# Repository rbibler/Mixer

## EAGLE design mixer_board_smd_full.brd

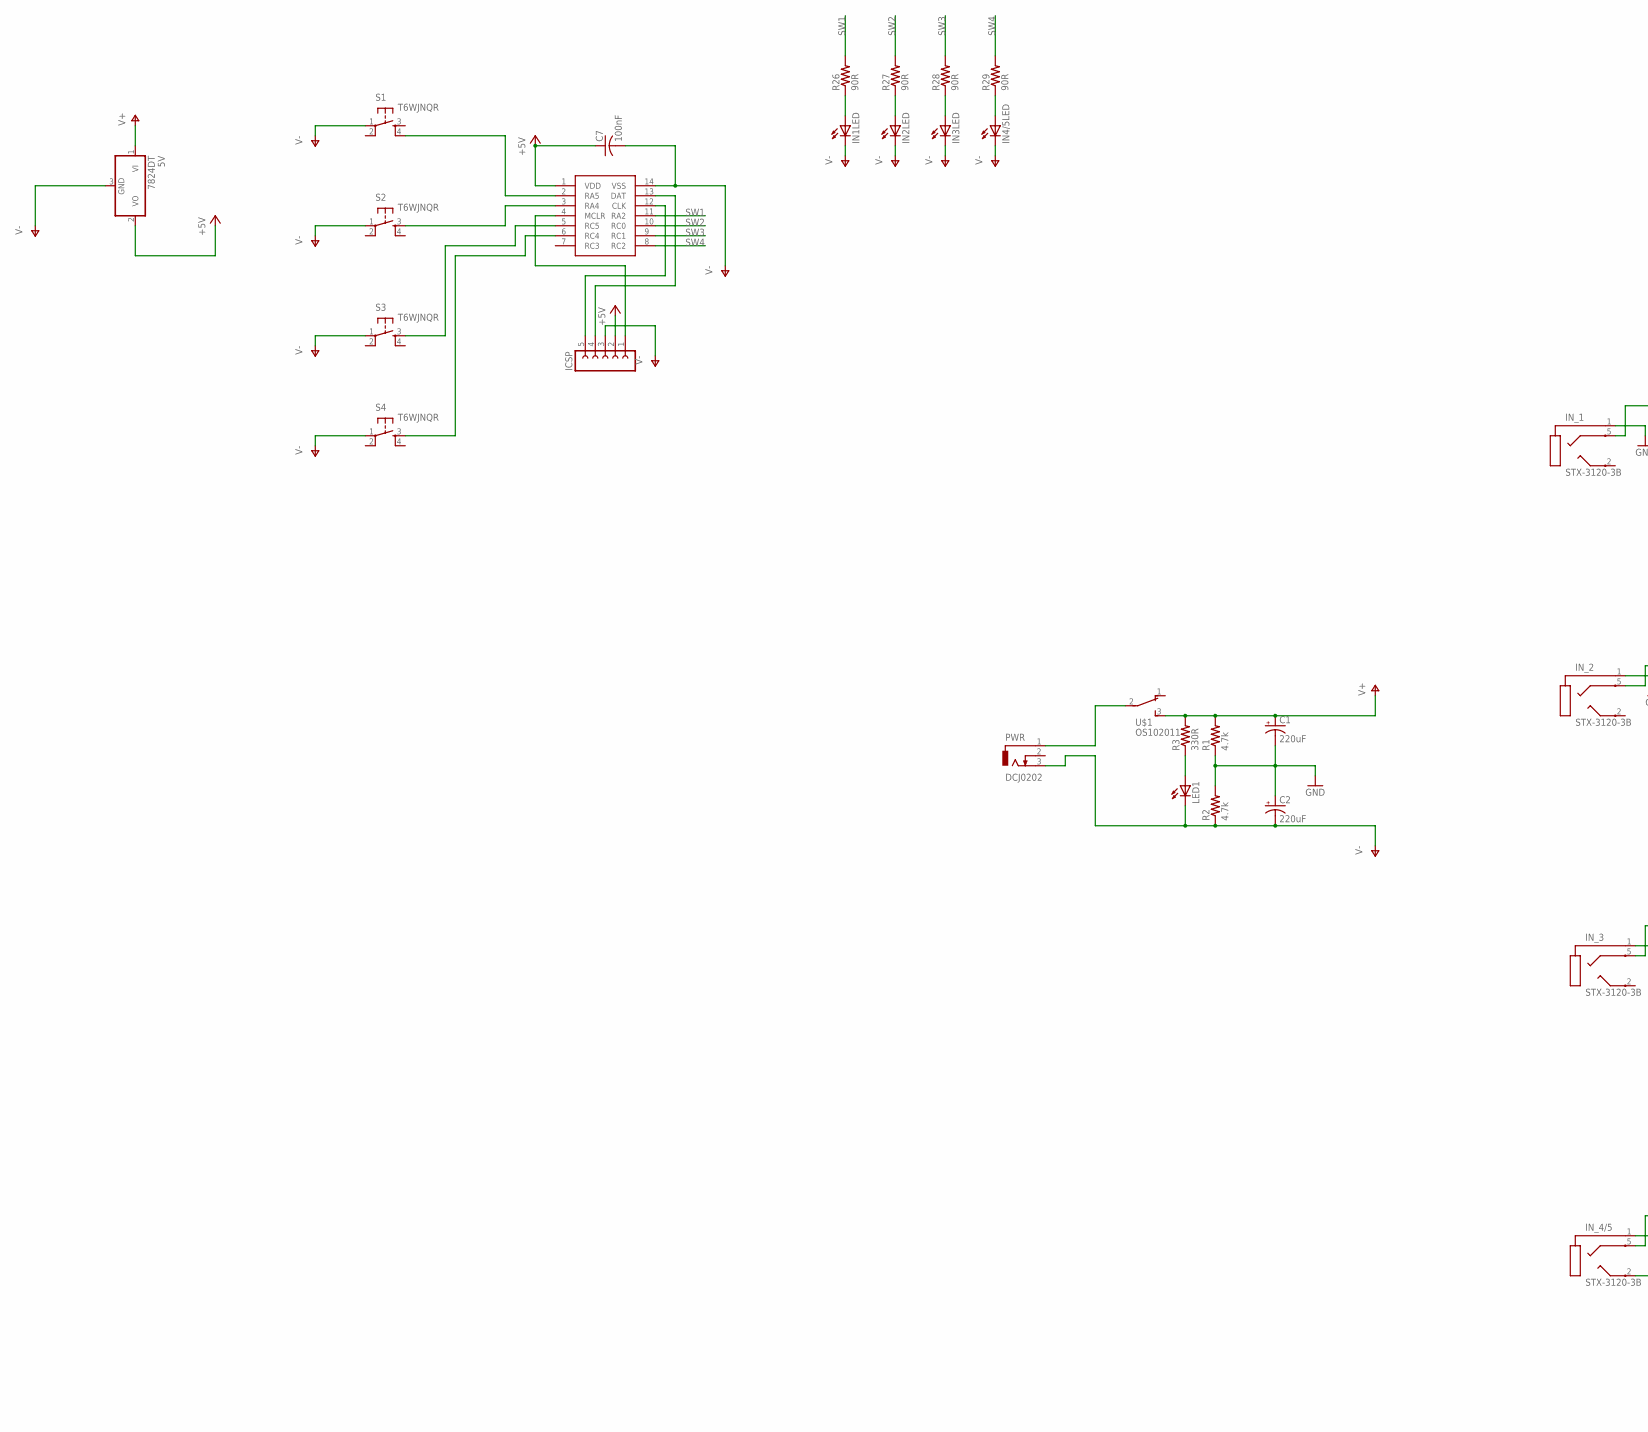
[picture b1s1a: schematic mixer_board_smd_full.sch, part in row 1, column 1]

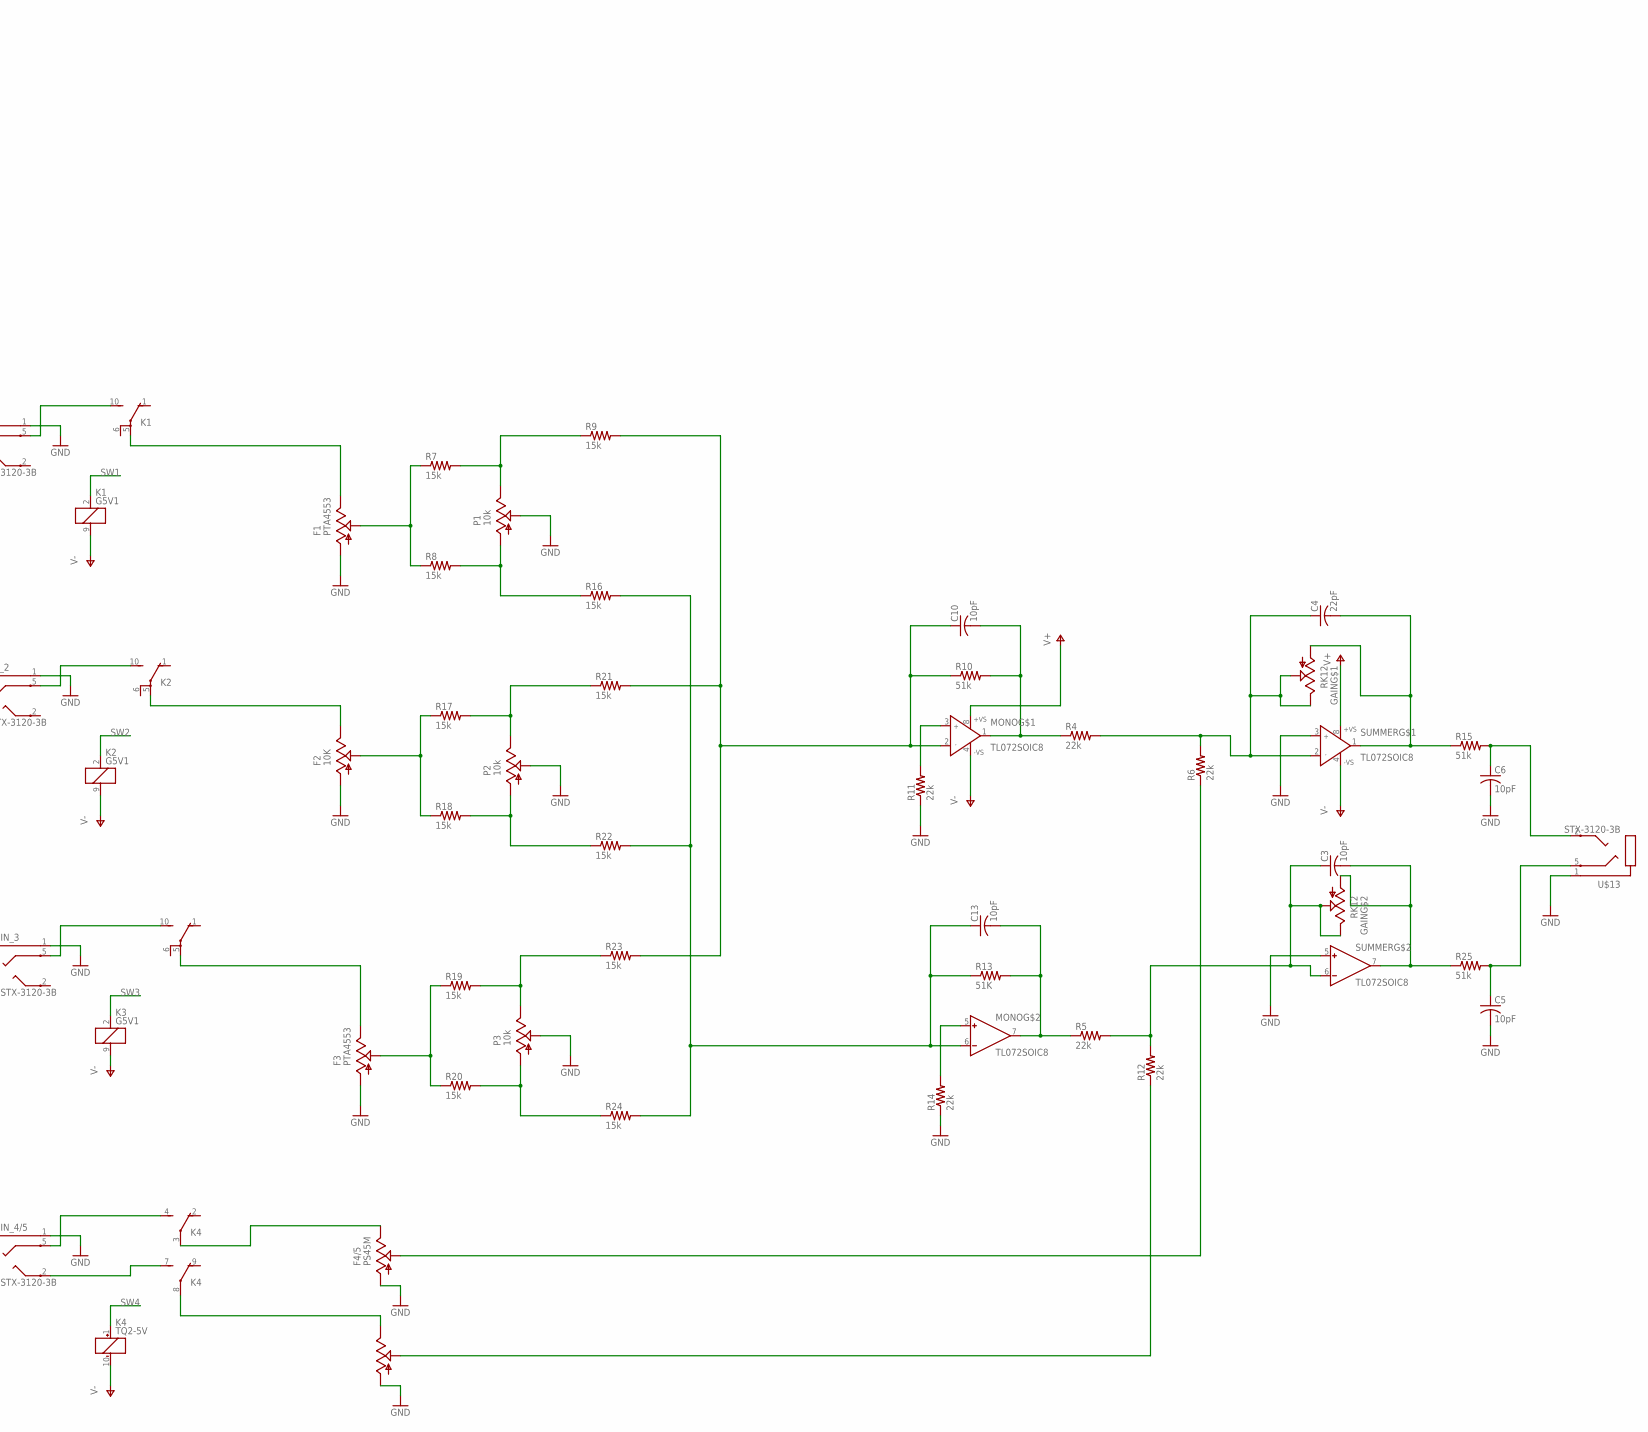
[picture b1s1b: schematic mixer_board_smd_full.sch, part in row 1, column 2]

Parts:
5V: 7824DT; TO252
C1, C2: 220uF; E1,8-4
C3, C5, C6, C10, C13: 10pF; C0805
C4: 22pF; C0805
C7: 100nF; C0805
F1, F3: PTA4553
F2: 10K; PTA4553
F4/5: PS45M
GAIN: RK12
ICSP: FE05-1
IN1LED, IN2LED, IN3LED, IN4/5LED: LEDCHIPLED_1206; CHIPLED_1206
IN_1, IN_2, IN_3, IN_4/5: STX-3120-3B; STX-3120
K1, K2, K3: G5V1
K4: TQ2-5V; TQ2
LED1: LEDCHIPLED_1206; CHIPLED_1206
MONO: TL072SOIC8; SOIC8
P1, P2, P3: 10k; PTV09A
PIC16: PIC16F18426; SO14
PWR: DCJ0202
R1, R2: 4.7k; M0805
R3: 330R; R0805
R4, R5, R6, R11, R12, R14: 22k; M0805
R7, R8, R9, R16, R17, R18, R19, R20, R21, R22, R23, R24: 15k; M0805
R10, R15, R25: 51k; M0805
R13: 51K; M0805
R26, R27, R28, R29: 90R; M0805
S1, S2, S3, S4: T6WJNQR; T6WJ2NGQR
SUMMER: TL072SOIC8; SOIC8
U$1: OS102011
U$13: STX-3120-3B; STX-3120

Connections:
+5V: 5V.2 (VO), C7.1, ICSP.2, PIC16.1 (VDD)
GND: C1.-, C2.+, C5.2, C6.2, F1.1, F2.1, F3.1, F4/5.1, F4/5.1', IN_1.1, IN_2.1, IN_3.1, IN_4/5.1, P1.2, P2.2, P3.2, R1.1, R2.2, R11.1, R14.1, SUMMER.3 (IN+), SUMMER.5 (IN+), U$13.1
unnamed: LED1.A, R3.1
unnamed: PIC16.2 (RA5), S1.4
unnamed: PIC16.3 (RA4), S2.3
unnamed: F4/5.3, K4.3
unnamed: F4/5.3', K4.8
unnamed: C4.2, GAIN.1, R15.1, SUMMER.1 (OUT)
unnamed: PIC16.5 (RC5), S3.3
unnamed: IN1LED.A, R26.1
unnamed: PIC16.6 (RC4), S4.3
unnamed: ICSP.1, PIC16.4 (MCLR)
unnamed: IN_4/5.5, K4.4 (S)
unnamed: IN_4/5.2, K4.7 (S)
unnamed: F1.2, R7.1, R8.1
unnamed: F4/5.2, R6.1
unnamed: P1.3, R7.2, R9.1
unnamed: P1.1, R8.2, R16.1
unnamed: C10.1, MONO.2 (IN-), R9.2, R10.1, R21.2, R23.2
unnamed: C10.2, MONO.1 (OUT), R4.1, R10.2
unnamed: C6.1, R15.2, U$13.2
unnamed: C4.1, GAIN.2, GAIN.3, R4.2, R6.2, SUMMER.2 (IN-)
unnamed: MONO.3 (IN+), R11.2
unnamed: P2.3, R17.2, R21.1
unnamed: C13.2, MONO.7 (OUT), R5.1, R13.2
unnamed: C5.1, R25.2, U$13.5
unnamed: MONO.5 (IN+), R14.2
unnamed: F4/5.2', R12.1
unnamed: IN2LED.A, R27.1
unnamed: C3.2, GAIN.1' (1), R25.1, SUMMER.7 (OUT)
unnamed: C13.1, MONO.6 (IN-), R13.1, R16.2, R22.2, R24.2
unnamed: P2.1, R18.2, R22.1
unnamed: IN3LED.A, R28.1
unnamed: C3.1, GAIN.2' (2), GAIN.3' (3), R5.2, R12.2, SUMMER.6 (IN-)
unnamed: IN4/5LED.A, R29.1
unnamed: P3.3, R19.2, R23.1
unnamed: P3.1, R20.2, R24.1
unnamed: F2.2, R17.1, R18.1
unnamed: ICSP.4, PIC16.13 (DAT)
unnamed: ICSP.5, PIC16.12 (CLK)
unnamed: F3.2, R19.1, R20.1
unnamed: IN_3.5, K3.10 (S)
unnamed: IN_2.5, K2.10 (S)
unnamed: IN_1.5, K1.10 (S)
unnamed: F2.3, K2.5
unnamed: F1.3, K1.5
unnamed: F3.3, K3.5
unnamed: PWR.1, U$1.2
SW1: K1.2 (1), PIC16.11 (RA2), R26.2
SW2: K2.2 (1), PIC16.10 (RC0), R27.2
SW3: K3.2 (1), PIC16.9 (RC1), R28.2
SW4: K4.1 (+), PIC16.8 (RC2), R29.2
V+: 5V.1 (VI), C1.+, MONO.8 (+VS), R1.2, R3.2, SUMMER.8 (+VS), U$1.3 (S)
V-: 5V.3 (GND), C2.-, C7.2, ICSP.3, IN1LED.C, IN2LED.C, IN3LED.C, IN4/5LED.C, K1.9 (2), K2.9 (2), K3.9 (2), K4.10 (-), LED1.C, MONO.4 (-VS), PIC16.14 (VSS), PWR.3, R2.1, S1.1, S2.1, S3.1, S4.1, SUMMER.4 (-VS)

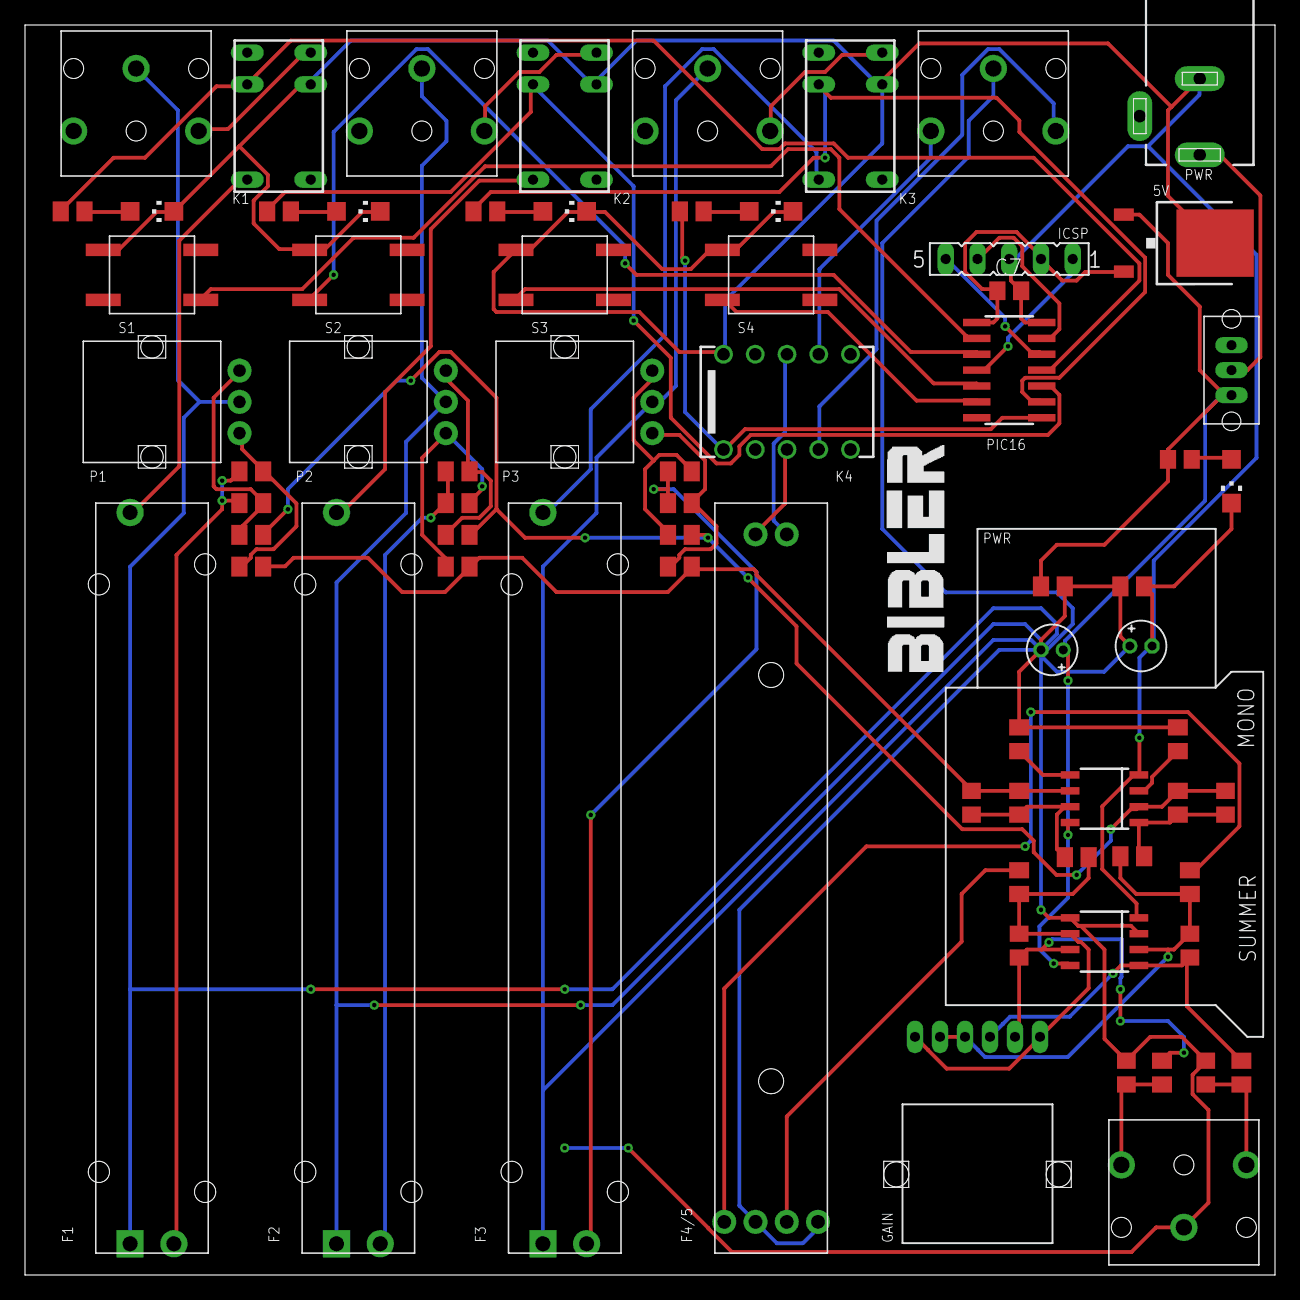
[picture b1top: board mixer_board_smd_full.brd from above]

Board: 2 copper layers, 100.0 x 100.0 mm, 71 parts (0 on the bottom side), 54 nets.

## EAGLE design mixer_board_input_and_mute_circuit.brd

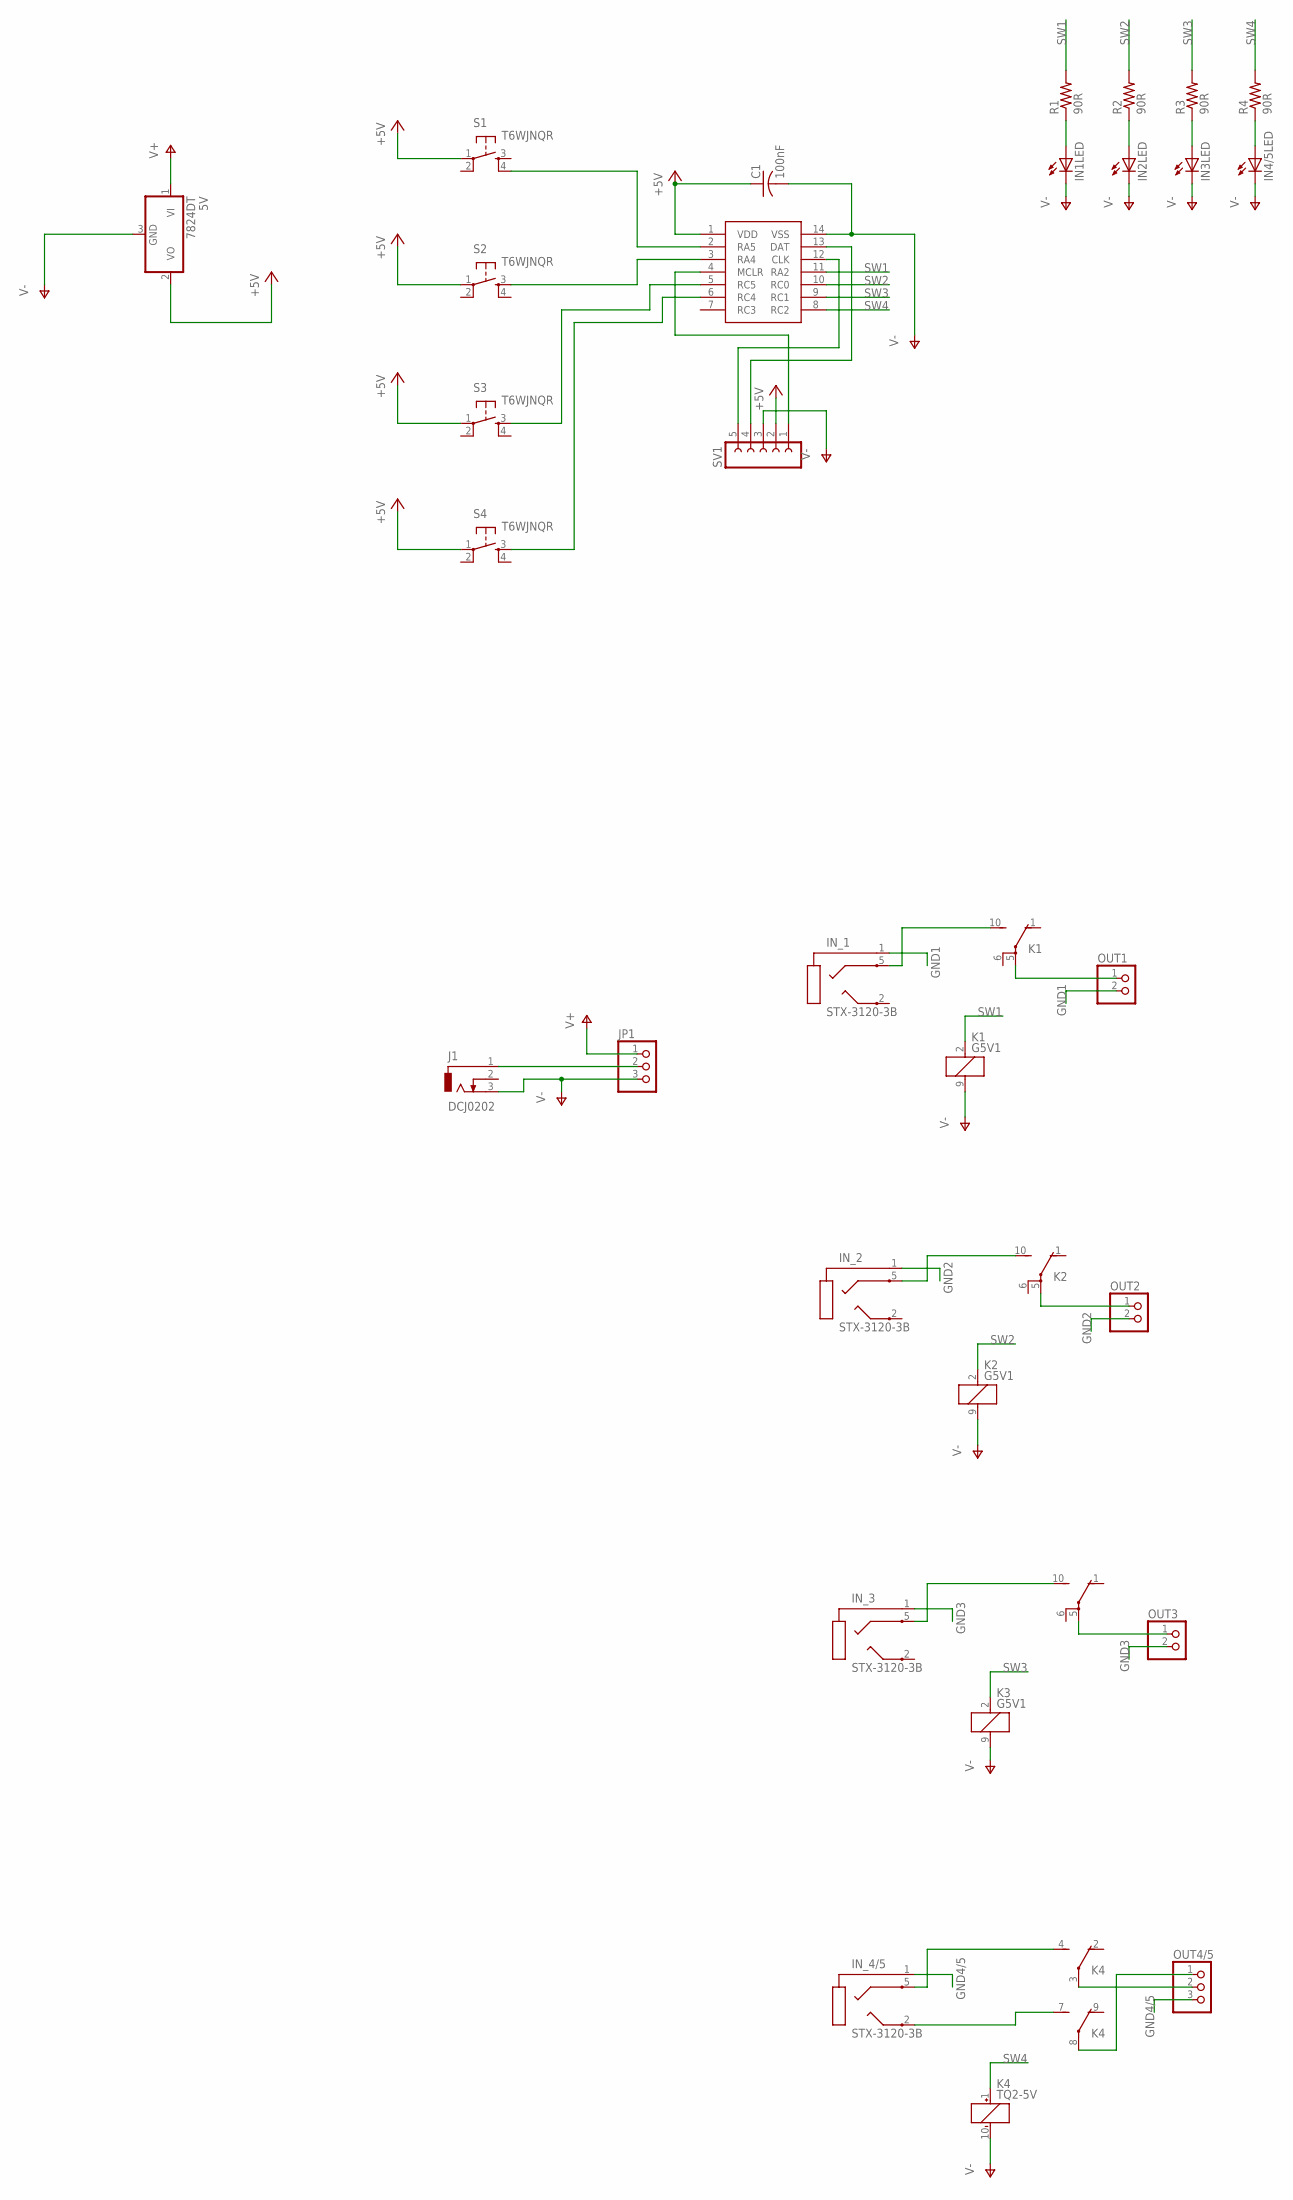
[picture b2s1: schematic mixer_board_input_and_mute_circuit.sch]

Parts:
5V: 7824DT; TO252
C1: 100nF; C0805
IN1LED, IN2LED, IN3LED, IN4/5LED: LEDCHIPLED_1206; CHIPLED_1206
IN_1, IN_2, IN_3, IN_4/5: STX-3120-3B; STX-3120
J1: DCJ0202
JP1: PINHD-1X3/90; 1X03/90
K1, K2, K3: G5V1
K4: TQ2-5V; TQ2
OUT1, OUT2, OUT3: PINHD-1X2/90; 1X02/90
OUT4/5: PINHD-1X3/90; 1X03/90
R1, R2, R3, R4: 90R; M0805
S1, S2, S3, S4: T6WJNQR; T6WJ2NGQR
SV1: FE05-1
U1: PIC16F18426; SO14

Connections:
+5V: 5V.2 (VO), C1.1, S1.1, S2.1, S3.1, S4.1, SV1.2, U1.1 (VDD)
GND1: IN_1.1, OUT1.2
GND2: IN_2.1, OUT2.2
GND3: IN_3.1, OUT3.2
GND4/5: IN_4/5.1, OUT4/5.3
unnamed: J1.1, JP1.2
unnamed: K4.3, OUT4/5.2
unnamed: S1.4, U1.2 (RA5)
unnamed: S2.3, U1.3 (RA4)
unnamed: K2.5, OUT2.1
unnamed: K1.5, OUT1.1
unnamed: K3.5, OUT3.1
unnamed: S3.3, U1.5 (RC5)
unnamed: IN1LED.A, R1.1
unnamed: S4.3, U1.6 (RC4)
unnamed: SV1.1, U1.4 (MCLR)
unnamed: IN_4/5.5, K4.4 (S)
unnamed: IN_4/5.2, K4.7 (S)
unnamed: K4.8, OUT4/5.1
unnamed: IN2LED.A, R2.1
unnamed: IN3LED.A, R3.1
unnamed: IN4/5LED.A, R4.1
unnamed: SV1.4, U1.13 (DAT)
unnamed: SV1.5, U1.12 (CLK)
unnamed: IN_3.5, K3.10 (S)
unnamed: IN_2.5, K2.10 (S)
unnamed: IN_1.5, K1.10 (S)
SW1: K1.2 (1), R1.2, U1.11 (RA2)
SW2: K2.2 (1), R2.2, U1.10 (RC0)
SW3: K3.2 (1), R3.2, U1.9 (RC1)
SW4: K4.1 (+), R4.2, U1.8 (RC2)
V+: 5V.1 (VI), JP1.1
V-: 5V.3 (GND), C1.2, IN1LED.C, IN2LED.C, IN3LED.C, IN4/5LED.C, J1.3, JP1.3, K1.9 (2), K2.9 (2), K3.9 (2), K4.10 (-), SV1.3, U1.14 (VSS)

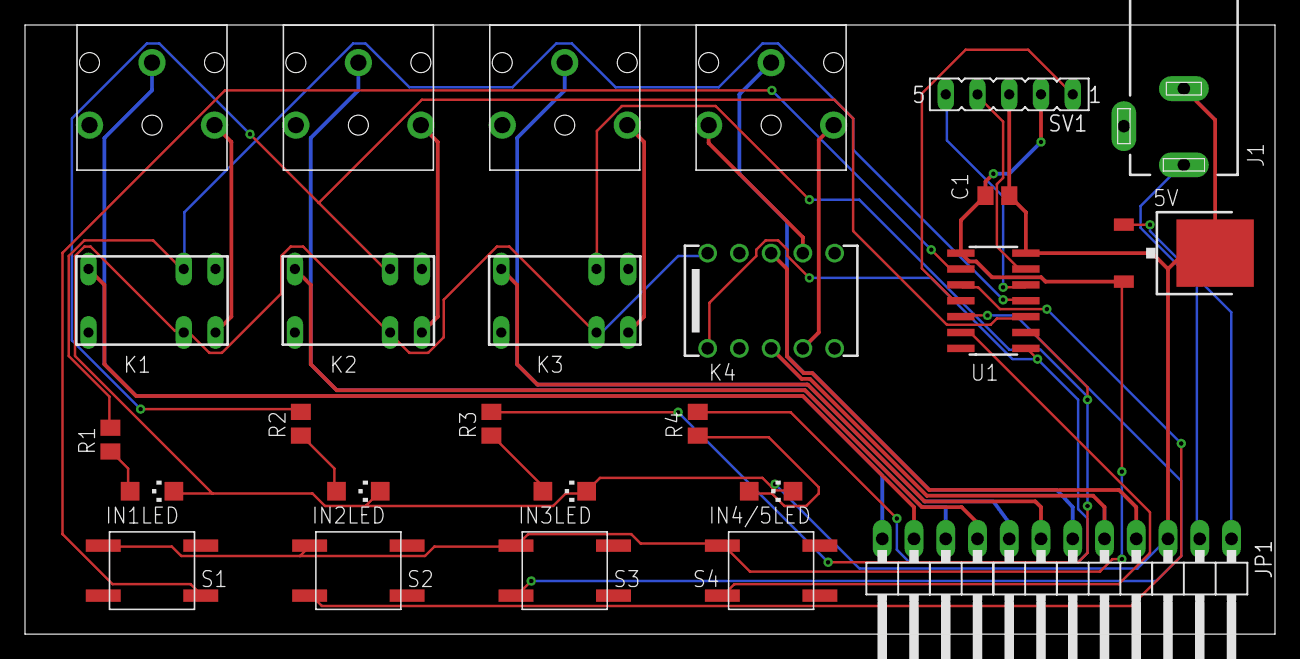
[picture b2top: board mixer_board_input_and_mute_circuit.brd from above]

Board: 2 copper layers, 100.0 x 48.7 mm, 30 parts (0 on the bottom side), 33 nets.

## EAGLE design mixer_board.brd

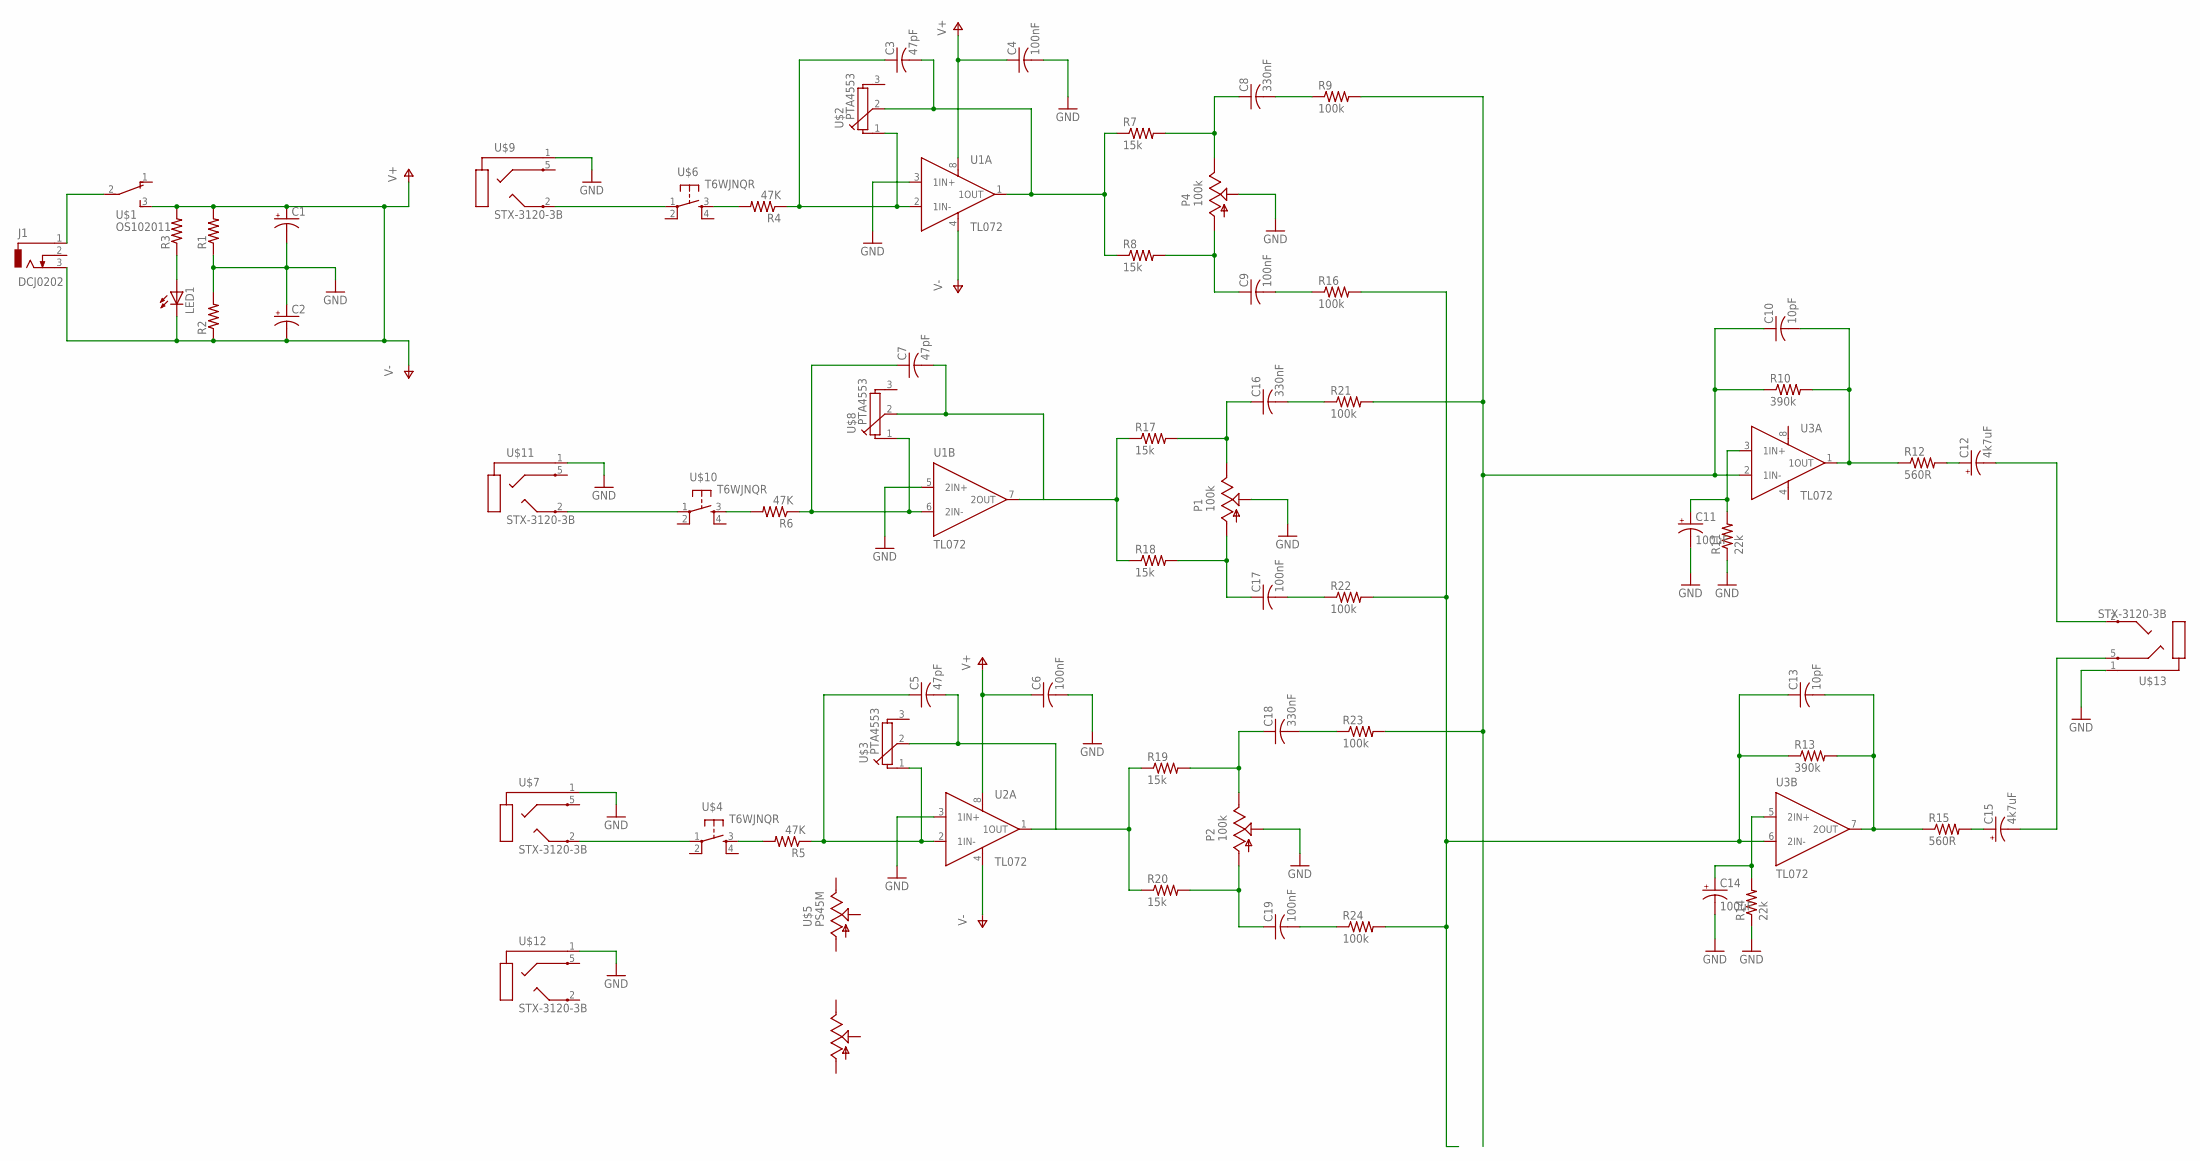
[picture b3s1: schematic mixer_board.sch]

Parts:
C1, C2: CPOL-US085CS-1R; 085CS_1R
C3, C5, C7: 47pF; C1206
C4, C6, C9, C17, C19: 100nF; C1206
C8, C16, C18: 330nF; C1206
C10, C13: 10pF; C1206
C11, C14: 100uF; 085CS_1R
C12, C15: 4k7uF; 085CS_1R
J1: DCJ0202
LED1: LEDCHIPLED_1206; CHIPLED_1206
P1, P2, P4: 100k; PTV09A
R1, R2, R3: R-US_M1406; M1406
R4, R5, R6: 47K; M1406
R7, R8, R17, R18, R19, R20: 15k; M1406
R9, R16, R21, R22, R23, R24: 100k; M1406
R10, R13: 390k; M1406
R11, R14: 22k; M1406
R12, R15: 560R; M1406
U1, U2, U3: TL072; DIP794W45P254L1060H508Q8
U$1: OS102011
U$2, U$3, U$8: PTA4553
U$4, U$6, U$10: T6WJNQR; T6WJ2NGQR
U$5: PS45M
U$7, U$9, U$11, U$12, U$13: STX-3120-3B; STX-3120

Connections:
GND: C1.-, C2.+, C4.2, C6.2, C11.-, C14.-, P1.2, P2.2, P4.2, R1.1, R2.2, R11.1, R14.1, U1.3 (1IN+), U1.5 (2IN+), U2.3 (1IN+), U$7.1, U$9.1, U$11.1, U$12.1, U$13.1
unnamed: J1.1, U$1.2
unnamed: LED1.A, R3.1
unnamed: U$4.1, U$7.2
unnamed: U$6.1, U$9.2
unnamed: C3.1, R4.1, U1.2 (1IN-), U$2.1 (1A)
unnamed: C3.2, R7.1, R8.1, U1.1 (1OUT), U$2.2 (1S)
unnamed: C5.1, R5.1, U2.2 (1IN-), U$3.1 (1A)
unnamed: R4.2, U$6.3
unnamed: C5.2, U2.1 (1OUT), U$3.2 (1S)
unnamed: R5.2, U$4.3
unnamed: U$10.1, U$11.2
unnamed: C7.1, R6.1, U1.6 (2IN-), U$8.1 (1A)
unnamed: C7.2, U1.7 (2OUT), U$8.2 (1S)
unnamed: R6.2, U$10.3
unnamed: C8.2, R9.1
unnamed: C8.1, P4.3, R7.2
unnamed: C9.1, P4.1, R8.2
unnamed: C10.1, R9.2, R10.1, R21.2, R23.2, U3.2 (1IN-)
unnamed: C10.2, R10.2, R12.1, U3.1 (1OUT)
unnamed: C12.-, U$13.2
unnamed: R17.1, R18.1
unnamed: C11.+, R11.2, U3.3 (1IN+)
unnamed: C16.1, P1.3, R17.2
unnamed: C13.2, R13.2, R15.1, U3.7 (2OUT)
unnamed: C12.+, R12.2
unnamed: C14.+, R14.2, U3.5 (2IN+)
unnamed: C15.+, R15.2
unnamed: C15.-, U$13.5
unnamed: C9.2, R16.1
unnamed: C13.1, R13.1, R16.2, R22.2, R24.2, U3.6 (2IN-)
unnamed: C17.1, P1.1, R18.2
unnamed: C16.2, R21.1
unnamed: C17.2, R22.1
unnamed: R19.1, R20.1
unnamed: C18.1, P2.3, R19.2
unnamed: C19.1, P2.1, R20.2
unnamed: C18.2, R23.1
unnamed: C19.2, R24.1
V+: C4.1, C6.1, U1.8 (VCC+), U2.8 (VCC+)
V-: C1.+, C2.-, J1.3, LED1.C, R1.2, R2.1, R3.2, U1.4 (VCC-), U2.4 (VCC-), U$1.3 (S)
VCC+: U3.8 (VCC+)
VCC-: U3.4 (VCC-)

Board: 2 copper layers, 64 parts (0 on the bottom side), 41 nets, no tracks yet.

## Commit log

2019-06-20 :lollipop: Added .gitattributes & .gitignore files
2019-06-20 Very first commit
    to the repo
2019-06-20 before auto router
2019-06-20 after auto router
2019-06-21 basically done
    circuit is confirmed. Need to double check layout and component
    footprints.
2019-06-21 I think it's done
    and ready to be shipped.
2019-06-26 all of the changes
2019-06-26 changed a few values
